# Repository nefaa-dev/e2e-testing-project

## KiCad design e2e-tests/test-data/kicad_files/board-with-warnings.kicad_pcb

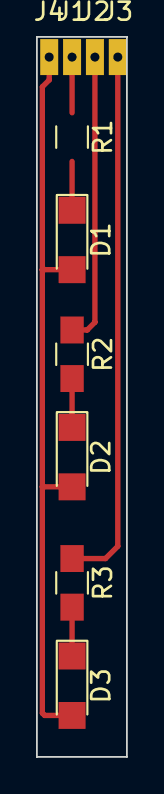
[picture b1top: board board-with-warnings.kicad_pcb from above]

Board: 2 copper layers, 5.0 x 40.0 mm, 10 parts (0 on the bottom side), 5 nets.

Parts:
D1, D2, D3: LED; LED_1206
J1, J2, J3, J4: Conn_01x01; SolderWirePad_single_0-8mmDrill
R1, R2, R3: 47R; R_0805_HandSoldering

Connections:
unnamed: D1.2, D2.2, D3.2, J4.1
unnamed: D2.1, R2.2
unnamed: D3.1, R3.2
unnamed: J2.1, R2.1
unnamed: J3.1, R3.1

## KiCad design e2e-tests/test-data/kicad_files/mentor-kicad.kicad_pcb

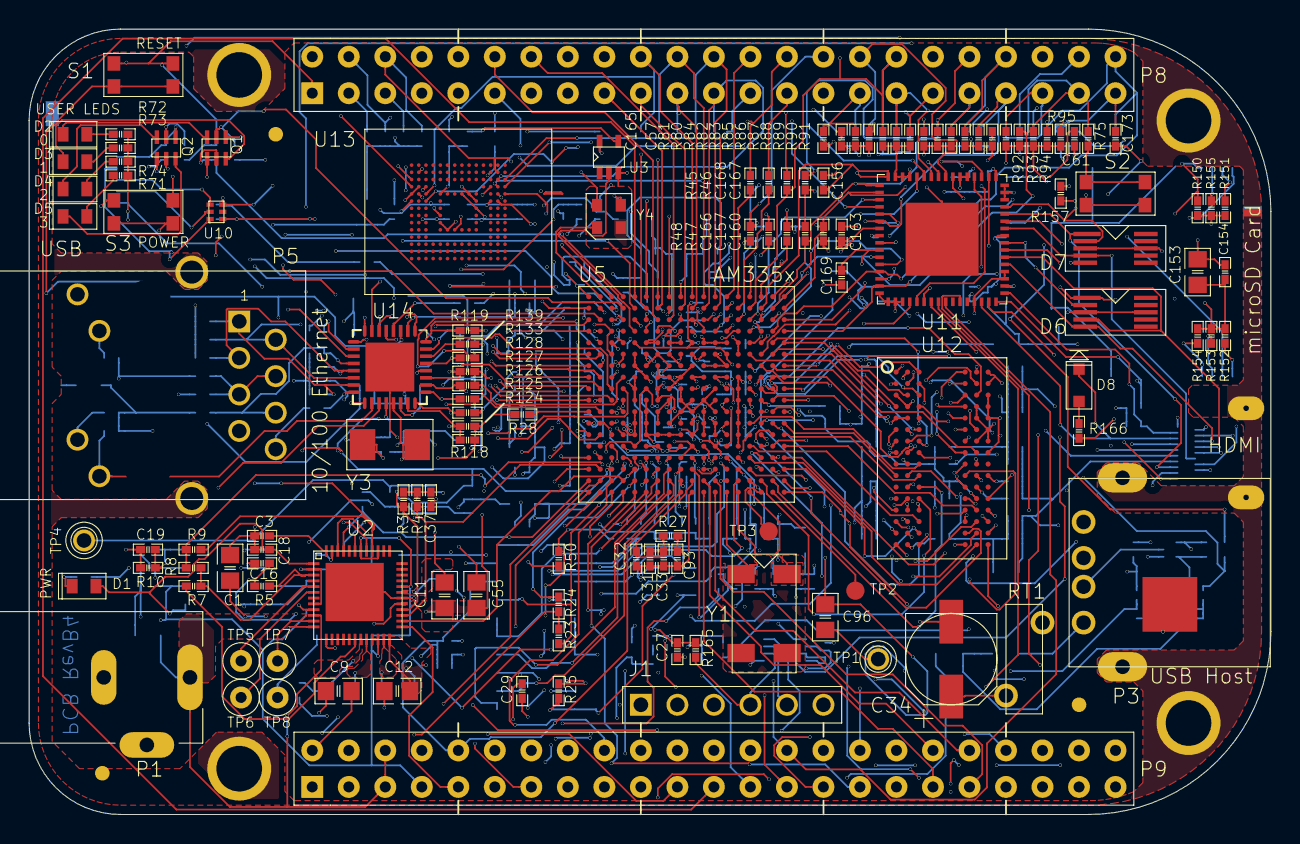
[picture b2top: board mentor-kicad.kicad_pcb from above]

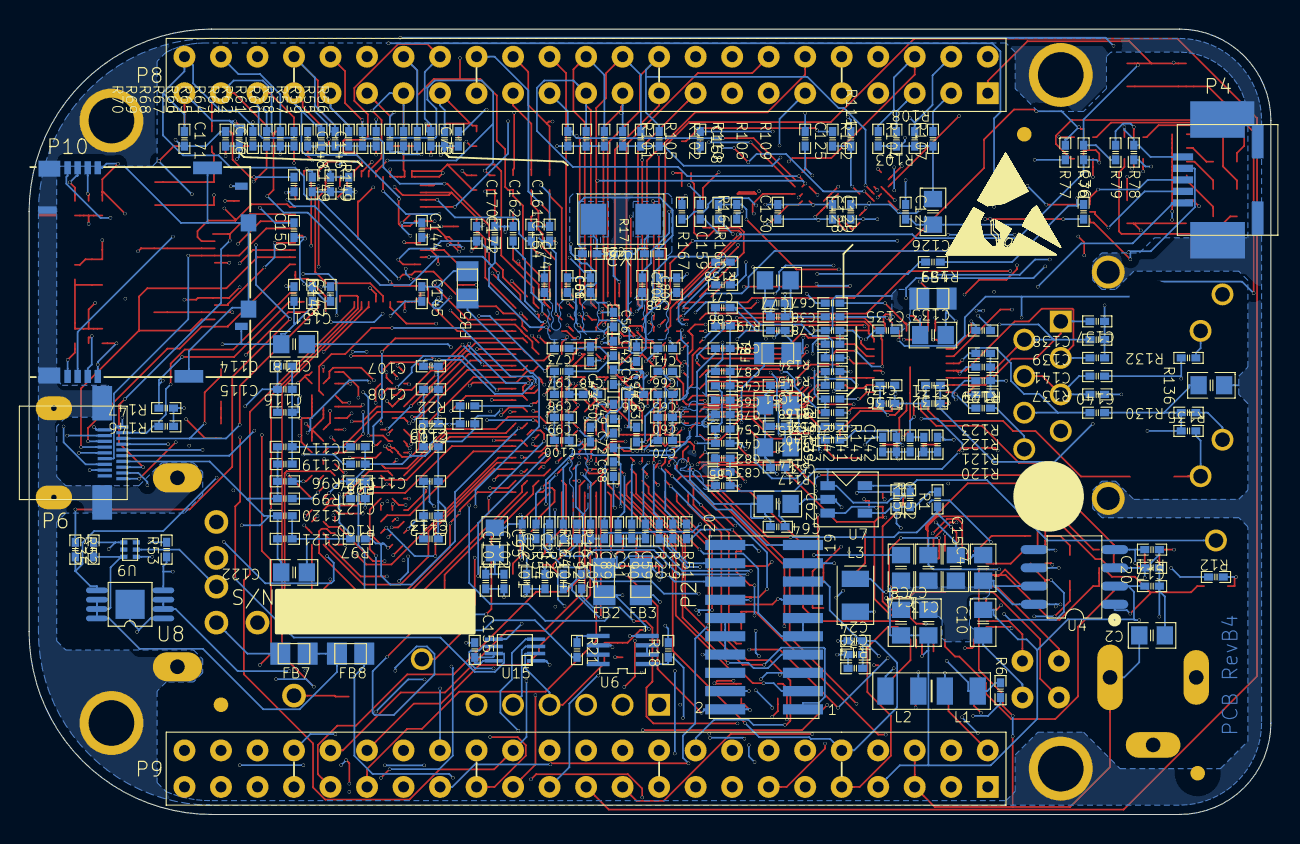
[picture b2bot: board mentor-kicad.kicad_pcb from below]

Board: 6 copper layers, 86.4 x 54.6 mm, 381 parts (250 on the bottom side), 310 nets.

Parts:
C1, C2, C4, C7, C8, C9, C10, C11, C12, C13, C14, C15, C39, C40, C55, C62, C77, C95, C96, C118, C122, C126, C133, C153: 10uF, 10V; 805
C3, C20, C27, C28, C29, C30, C31, C33, C35, C36, C37, C38, C41, C42, C43, C44, C45, C46, C47, C48, C49, C50, C51, C52, C53, C54, C56, C57, C58, C59, C60, C61, C63, C64, C65, C66, C67, C68, C69, C70, C71, C72, C73, C74, C75, C76, C78, C79, C80, C81, C82, C83, C84, C85, C86, C87, C88, C92, C93, C94, C97, C98, C99, C100, C101, C102, C103, C105, C106, C107, C108, C109, C110, C111, C112, C113, C114, C115, C116, C117, C119, C120, C121, C124, C127, C128, C129, C130, C131, C132, C135, C145, C147, C149, C150, C152, C154, C155, C158, C159: 0.1uf, 6V3; 402
C16, C17, C18, C125, C144, C146, C148, C151: 2.2uF, 6V3; 402
C19, C136: 470pF, 50V; 402
C21, C22, C25, C26: 18pF, 50V; 402
C24, C89, C90, C91, C104, C134: 1uF, 10V; 402
C32, C123: 1nF, 50V; 402
C34: 100uF, 6V3; RD205SMD_250D
C137, C138, C139, C140: 15pF, DNI; 402
C141: 0.022uF,10V; 402
C142, C143: 30pF, 50V; 402
C156, C157, C160, C161, C162, C163, C164, C165, C166, C167, C168, C169, C170, C171, C172, C173: 47pF, 6.3V; 402
D1, D2, D3, D4, D5: 598-8170-107F; LED_0603
D6, D7: IP4283CZ10-TT; TSSOP10
D8: RB751V40,115; SOD323
FB1, FB2, FB3, FB4, FB5, FB7: 150OHM800mA; SM-7351-IND-0805
FB8: 0.1 Ohm, 0805; SM-7351-IND-0805
J1: HEADER 6; SIP6
L1, L2, L3: 2.2uH, 2.6A; 2520
MTG1, MTG2, MTG3, MTG4: MHOLE; MTGH200C125D_PL
P1: PJ-200A; CONN3-PWR-PJ102A
P2: CTI JTAG,DNI; HEADER10X2_SMD
P3: USB-A Conn. - 87520-xx1xx; USB_A_SH
P4: mini USB-B; USB5MINI_4SHIELDED_SMD-5
P5: WE_7499010211A; RJ45-7499010211A
P6: 10118241-001RLF; CONN19_HDMI
P8, P9: FEMALE HEADER 2x23; HEADER23X2
P10: MOLEX 502570-001; SD-MICRO-SCHA5B0300
Q1, Q2: DMC56404; SMINI6-F3-B
R1, R56, R65, R66, R67, R68, R76, R77, R78, R79, R80, R82, R83, R84, R85, R86, R87, R88, R89, R94, R95, R165: 100K, 1%; 402
R3, R4, R97, R112, R113, R114, R119, R146, R147: 1.5K, 1%; 402
R5, R6, R7, R8, R19, R20, R27, R49, R50, R51, R137, R142, R149, R159, R160, R161, R162: 0R, 1%; 402
R9: 0R, 1%, DNI; 402
R10: 470K, 5%; 402
R11: 280K, 1%; 402
R12, R71, R72, R73, R74: 820, 5%; 402
R14: 10K, 1%; 402
R17: 1M, 1%; 402
R18, R21, R28, R45, R46, R47, R48, R167: 33, 0402; 402
R22, R120, R121, R122, R123: 49.9, 1%; 402
R23, R24, R25, R26, R163, R164: 4.75K, 1%; 402
R52, R53, R54, R96, R98, R100, R101, R102, R103, R104, R105, R106, R107, R108, R109, R110, R111, R115, R116, R117, R118, R135, R145, R148, R150, R151, R152, R153, R154, R155, R156, R157, R158: 10k, 1%; 402
R55, R57, R59, R69, R81, R90, R91, R92, R93: 100K, 1%, DNI; 402
R58, R60, R61, R62, R63, R64, R70: 100K, 1%,DNI; 402
R75: 100; 402
R99: 240, 1%; 402
R124: 10, 1%,DNI; 402
R125, R126, R127, R128, R129, R131, R133, R134, R138, R139: 100, 1%; 402
R130, R132: 470, 5%; 402
R136: 0.1, 0805; 805
R140: 0R, 1%,DNI; 402
R141: 1M, 1%,DNI; 402
R143: 10, 1%; 402
R144: 12.1K, 1%; 402
R166: 27K, 1%; 402
RT1: PTC_RXEF010; POLYSW200-5638-310
S1, S2, S3: KMR231GLFS; SW4SMD_63X161LS
TP1, TP4: TESTPT1; TP1-8040
TP2, TP3: TESTPT1; TP60C_SMD
TP5, TP6, TP7, TP8: TESTPT1; TP60C33D
U2: TPS65217C; U_48_RSL
U3: SN74LVC1G06DCK; DCK5_2P15X1P4
U4: TL5209; SO8-25X75
U5: IC_AM335X_ZCE_1; AM33XX_15X15
U6: SN74LVC1G74DCTR; SOP8_DCT
U7: 24LC32A; SOT23-5
U8: TPS2051 (DGN); DGN-16X60
U9, U10: TPD4S012; U_6_DRY
U11: TDA19988; QFN64S9X9P5
U12: MT41K256M16HA -125:E; BGA96_T9_P8_9X14
U13: eMMC, 2GB; BGA153_P14_P5_11P5X13
U14: LAN8710A; QFN32_5X5MM_EP3P3MM
U15: SN74LVC2G241; U_8_DCU
Y1: 32.768kHz; XTAL4_126-216SMD
Y2: 24MHz; XTAL150SMD_125X196
Y3: 25.000MHz; XTAL150SMD_125X196
Y4: 24.576MHz; OSC4_61X65LS_79X98SMD

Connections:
12MHZ: R21.2, U11.27
12M_LOOP: U6.2, U6.3
AIN0: P9.39, U5.B6
AIN1: P9.40, U5.C7
AIN2: P9.37, U5.B7
AIN3: P9.38, U5.A7
AIN4: P9.33, U5.C8
AIN5: P9.36, U5.B8
AIN6: P9.35, U5.A8
AIN7: R163.2, R164.1, U5.C9
B_UART0_RX: J1.4, R165.1, U15.2
B_UART0_TX: J1.5, U15.3
CAP_VBB_MPU: C91.1, U5.C10
CAP_VDD_SRAM_CORE: C89.1, U5.D9
CAP_VDD_SRAM_MPU: C90.1, U5.D11
CLKOUT2: P2.18, P9.41, R19.2, R20.1
CLKOUT_SRC: R19.1, U5.D14
CRS: R139.2, U14.14
DDR_A0: U5.F3, U12.N3
DDR_A1: U5.H1, U12.P7
DDR_A2: U5.E4, U12.P3
DDR_A3: U5.C3, U12.N2
DDR_A4: U5.C2, U12.P8
DDR_A5: U5.B1, U12.P2
DDR_A6: U5.D5, U12.R8
DDR_A7: U5.E2, U12.R2
DDR_A8: U5.D4, U12.T8
DDR_A9: U5.C1, U12.R3
DDR_A10: U5.F4, U12.L7
DDR_A11: U5.F2, U12.R7
DDR_A12: U5.E3, U12.N7
DDR_A13: U5.H3, U12.T3
DDR_A14: U5.H4, U12.T7
DDR_A15: U5.D3, U12.M7
DDR_BA0: U5.C4, U12.M2
DDR_BA1: U5.E1, U12.N8
DDR_BA2: U5.B3, U12.M3
DDR_CASN: U5.F1, U12.K3
DDR_CKE: R96.2, U5.G3, U12.K9
DDR_CLK: U5.D2, U12.J7
DDR_CLKN: U5.D1, U12.K7
DDR_CSN: U5.H2, U12.L2
DDR_D0: U5.M3, U12.E3
DDR_D1: U5.M4, U12.F7
DDR_D2: U5.N1, U12.F2
DDR_D3: U5.N2, U12.F8
DDR_D4: U5.N3, U12.H3
DDR_D5: U5.N4, U12.H8
DDR_D6: U5.P3, U12.G2
DDR_D7: U5.P4, U12.H7
DDR_D8: U5.J1, U12.D7
DDR_D9: U5.K1, U12.C3
DDR_D10: U5.K2, U12.C8
DDR_D11: U5.K3, U12.C2
DDR_D12: U5.K4, U12.A7
DDR_D13: U5.L3, U12.A2
DDR_D14: U5.L4, U12.B8
DDR_D15: U5.M1, U12.A3
DDR_DQM0: U5.M2, U12.E7
DDR_DQM1: U5.J2, U12.D3
DDR_DQS0: U5.P1, U12.F3
DDR_DQS1: U5.L1, U12.C7
DDR_DQSN0: U5.P2, U12.G3
DDR_DQSN1: U5.L2, U12.B7
DDR_ODT: U5.G1, U12.K1
DDR_RASN: U5.G4, U12.J3
DDR_RESETN: R97.2, U5.G2, U12.T2
DDR_VREF: C28.1, C123.1, C124.1, R98.2, R100.1, U5.J4, U12.H1, U12.M8
DDR_VTP: R22.2, U5.J3
DDR_WEN: U5.B2, U12.L3
DGND: C1.1, C2.1, C3.1, C4.1, C7.1, C8.1, C9.1, C10.1, C11.1, C12.1, C13.1, C14.1, C15.1, C16.2, C17.2, C18.2, C19.2, C20.2, C24.2, C27.2, C28.2, C29.2, C30.2, C34.2, C35.2, C36.2, C37.2, C38.2, C39.1, C40.1, C41.2, C42.2, C43.2, C44.2, C45.2, C46.2, C47.2, C48.2, C49.2, C50.2, C51.2, C52.2, C53.2, C54.2, C55.1, C56.1, C57.1, C58.2, C59.2, C60.1, C61.1, C62.1, C63.2, C64.2, C65.2, C66.2, C67.2, C68.1, C69.1, C70.1, C71.1, C72.1, C73.1, C74.1, C75.1, C76.1, C77.2, C78.2, C79.2, C80.2, C81.2, C82.2, C83.2, C84.2, C85.2, C86.2, C87.2, C88.2, C89.2, C90.2, C91.2, C92.2, C94.2, C95.1, C96.1, C97.2, C98.2, C99.2, C100.2, C101.2, C102.2, C103.2, C104.2, C105.2, C106.2, C107.2, C108.2, C109.2, C110.2, C111.2, C112.2, C113.2, C114.2, C115.2, C116.2, C117.2, C118.1, C119.2, C120.2, C121.2, C122.1, C123.2, C124.2, C125.2, C126.1, C127.2, C128.2, C129.2, C130.2, C131.2, C132.2, C133.1, C134.2, C135.2, C136.2, C137.2, C138.2, C139.2, C140.2, C141.2, C142.2, C143.2, C144.2, C145.2, C146.2, C147.2, C148.2, C149.2, C150.2, C151.2, C152.2, C153.2, C154.2, C155.1, C156.2, C157.2, C158.2, C159.2, C160.2, C161.2, C162.2, C163.2, C164.2, C165.2, C166.2, C167.2, C168.2, C169.2, C170.2, C171.2, C172.2, C173.2, D6.3, D6.8, D7.3, D7.8, FB3.2, J1.1, P1.2, P2.4, P2.8, P2.10, P2.12, P2.16, P2.20, P3.4, P4.5, P5.8, P6.4, P6.7, P6.10, P6.13, P6.16, P8.1, P8.2, P9.1, P9.2, P9.43, P9.44, P9.45, P9.46, P10.6, P10.9, Q1.1, Q1.4, Q2.1, Q2.4, R10.2, R12.1, R22.1, R25.2, R49.1, R53.2, R54.1, R76.2, R77.2, R78.2, R79.2, R80.2, R81.2, R82.2, R83.2, R84.2, R85.2, R86.2, R87.2, R88.2, R89.2, R90.2, R91.2, R92.2, R93.2, R94.2, R95.2, R96.1, R99.1, R100.2, R115.2, R116.2, R117.2, R118.2, R130.1, R132.1, R135.2, R136.1, R144.2, R145.2, R148.2, R149.2, R164.2, R165.2, S1.1, S1.3, S2.2, S2.4, S3.1, S3.3, TP1.1, TP8.1, U2.30, U2.41, U2.49, U3.3, U4.5, U4.6, U4.7, U4.8, U5.A1, U5.A18, U5.F8, U5.G8, U5.G9, U5.G11, U5.G12, U5.H6, U5.H7, U5.H8, U5.H9, U5.H10, U5.H12, U5.J6, U5.J7, U5.J8, U5.J9, U5.J10, U5.J11, U5.K7, U5.K9, U5.K10, U5.K11, U5.L10, U5.L11, U5.L12, U5.L13, U5.M6, U5.M7, U5.M8, U5.M9, U5.M10, U5.M12, U5.M14, U5.N7, U5.N10, U5.N11, U5.N14, U5.V1, U5.V18, U6.4, U7.2, U8.1, U8.9, U9.4, U10.4, U11.8, U11.9, U11.16, U11.17, U11.18, U11.19, U11.53, U11.54, U11.61, U11.62, U11.63, U11.65, U12.A9, U12.B1, U12.B3, U12.B9, U12.D1, U12.D8, U12.E1, U12.E2, U12.E8, U12.F9, U12.G1, U12.G8, U12.G9, U12.J2, U12.J8, U12.M1, U12.M9, U12.P1, U12.P9, U12.T1, U12.T9, U13.C4, U13.E7, U13.G5, U13.H10, U13.K8, U13.N2, U13.N5, U13.P4, U13.P6, U14.33, U15.1, U15.4, Y4.2
DVI_+5V: P6.19, R146.1, R147.1, RT1.2
EHRPWM1A: P9.14, U5.U14
EHRPWM1B: P9.16, U5.T14
EHRPWM2A: P8.19, U5.U10
EHRPWM2B: P8.13, U5.T10
EMMC_RSTN: R111.2, R162.2, U13.K5
EMMC_VCCI: C125.1, U13.C2
ENZ_KALDO_1P8V: R54.2, U5.B4
ETH_TXD4: R145.1, U14.18
GNDA_ADC: C31.2, C32.2, C33.2, C93.2, FB3.1, P9.34, U5.A9, U5.E8
GND_EARTH: MTG1.1, MTG2.1, MTG3.1, MTG4.1, P3.5, P3.6, P4.6, P4.7, P4.8, P4.9, P5.13, P5.14, P6.20, P6.21, P6.22, P6.23, P10.11, P10.12, P10.13, P10.14, P10.15, P10.16, R136.2
GND_OSC0: C25.2, C26.2, U5.V11
GND_OSC1: C21.1, C22.1, U5.A5
GPIO0_7: P9.42, R50.1, R51.1
GPIO0_7SRC: R50.2, U5.C18
GPIO0_26: P8.14, U5.T11
GPIO0_27: P8.17, U5.U12
GPIO1_12: P8.12, U5.T12
GPIO1_13: P8.11, U5.R12
GPIO1_14: P8.16, U5.V13
GPIO1_15: P8.15, U5.U13
GPIO1_16: P9.15, R160.2, R161.2
GPIO1_17: P9.23, U5.V14
GPIO1_28: P9.12, U5.U18
GPIO1_29: P8.26, U5.V6
GPIO2_1: P8.18, U5.V12
GPIO3_18: R51.2, U5.B12
GPIO3_19: P9.27, U5.C13
GPIO3_20: R20.2, U5.D13
GPIO3_21: P9.25, R167.2, U5.A14
GRNA: P5.9, U14.3
GRN_C: P5.10, R132.2
HDMICLK_DISN: U5.V17, Y4.1
HDMI_1V8: C144.1, C145.1, C146.1, C147.1, C148.1, C149.1, C150.1, C151.1, FB5.1, U11.5, U11.14, U11.29, U11.35, U11.36, U11.41, U11.46, U11.47, U11.48, U11.55
HDMI_CEC: D8.1, P6.15, U11.30
HDMI_CEC_D: D8.2, R166.1
HDMI_DSCL: P6.17, R146.2, U11.33
HDMI_DSDA: P6.18, R147.2, U11.32
HDMI_HPD: P6.1, U11.31
HDMI_INT: R158.2, U5.U16, U11.50
HDMI_SWING: R148.1, U11.34
HDMI_TX0+: D6.2, P6.9, U11.40
HDMI_TX0-: D6.1, P6.11, U11.39
HDMI_TX1+: D7.5, P6.6, U11.43
HDMI_TX1-: D7.4, P6.8, U11.42
HDMI_TX2+: D7.2, P6.3, U11.45
HDMI_TX2-: D7.1, P6.5, U11.44
HDMI_TXC+: D6.4, P6.12, U11.38
HDMI_TXC-: D6.5, P6.14, U11.37
I2C0_SCL: R3.2, U2.28, U5.C16, U7.1, U11.52
I2C0_SDA: R4.2, U2.27, U5.C17, U7.3, U11.51
I2C1_SCL: P9.17, U5.A16
I2C1_SDA: P9.18, U5.B16
I2C2_SCL: P9.19, U5.D17
I2C2_SDA: P9.20, U5.D18
JTAG_EMU0: P2.13, R23.2, U5.C14
JTAG_EMU1: P2.14, R24.2, U5.B14
JTAG_TCK: P2.9, P2.11, U5.A12
JTAG_TDI: P2.3, U5.B11
JTAG_TDO: P2.7, U5.A11
JTAG_TMS: P2.1, U5.C11
JTAG_TRSTN: P2.2, R25.1, U5.B10
LCDDE: R48.1, U5.R6
LCDPCLK: R45.1, U5.V5
LCDVHYNC: R47.1, U5.R5
LCDVSYNC: R46.1, U5.U5
LCD_DATA0: C173.1, P8.45, R70.2, R95.1, U5.R1, U11.15
LCD_DATA1: C171.1, P8.46, R69.2, R94.1, U5.R2, U11.13
LCD_DATA2: C172.1, P8.43, R68.2, R75.1, R93.1, U5.R3, U11.12
LCD_DATA3: C170.1, P8.44, R67.2, R92.1, U5.R4, U11.11
LCD_DATA4: C169.1, P8.41, R66.2, R91.1, U5.T1, U11.10
LCD_DATA5: C163.1, P8.42, R65.2, R90.1, U5.T2, U11.7
LCD_DATA6: C162.1, P8.39, R64.2, R89.1, U5.T3, U11.6
LCD_DATA7: C161.1, P8.40, R63.2, R88.1, U5.T4, U11.3
LCD_DATA8: C160.1, P8.37, R62.2, R87.1, U5.U1, U11.2
LCD_DATA9: C157.1, P8.38, R61.2, R86.1, U5.U2, U11.1
LCD_DATA10: C156.1, P8.36, R60.2, R85.1, U5.U3, U11.64
LCD_DATA11: C168.1, P8.34, R59.2, R84.1, U5.U4, U11.60
LCD_DATA12: C167.1, P8.35, R58.2, R83.1, U5.V2, U11.59
LCD_DATA13: C166.1, P8.33, R57.2, R82.1, U5.V3, U11.58
LCD_DATA14: C165.1, P8.31, R56.2, R81.1, U5.V4, U11.57
LCD_DATA15: C164.1, P8.32, R55.2, R80.1, U5.T5, U11.56
LCD_DE: P8.30, R48.2, U11.20
LCD_HSYNC: P8.29, R47.2, U11.22
LCD_PCLK: P8.28, R45.2, U11.4
LCD_VSYNC: P8.27, R46.2, U11.21
LDO_PGOOD: U2.46, U5.B5
LEDAA: D2.2, R72.2
LEDAC: D2.1, Q1.6
LEDBA: D3.2, R73.2
LEDBC: D3.1, Q1.3
LEDCA: D4.2, R74.2
LEDCC: D4.1, Q2.6
LEDDA: D5.2, R71.2
LEDDC: D5.1, Q2.3
MDIO_CLK: U5.M18, U14.17
MDIO_DATA: R119.2, U5.M17, U14.16
MII1_COL: R138.1, U5.H16
MII1_CRS_DV: R139.1, U5.H17
MII1_REFCLK: R28.2, R124.1, R140.1
MII1_RXCLK: R131.1, U5.L18
MII1_RXD0: R128.1, U5.M16
MII1_RXD1: R127.1, U5.L15
MII1_RXD2: R126.1, U5.L16
MII1_RXD3: R125.1, U5.L17
MII1_RXDV: R129.1, U5.J17
MII1_RXERR: R133.1, U5.J15
MII1_TXCLK: R134.1, U5.K18
MII1_TXD0: U5.K17, U14.22
MII1_TXD1: U5.K16, U14.23
MII1_TXD2: U5.K15, U14.24
MII1_TXD3: U5.J18, U14.25
MII1_TXEN: U5.J16, U14.21
MMC0_CD: P2.19, P10.10, R157.1, U5.C15
MMC0_CLKO: P10.5, R152.2, U5.G17
MMC0_CMD: P10.3, R151.2, U5.G18
MMC0_DAT0: P10.7, R153.2, U5.G16
MMC0_DAT1: P10.8, R154.2, U5.G15
MMC0_DAT2: P10.1, R150.2, U5.F18
MMC0_DAT3: P10.2, R155.2, U5.F17
MMC1_CLK: P8.21, R110.2, U5.U9, U13.M6
MMC1_CMD: P8.20, R109.2, U5.V9, U13.M5
MMC1_DAT0: P8.25, R101.2, U5.U7, U13.A3
MMC1_DAT1: P8.24, R102.2, U5.V7, U13.A4
MMC1_DAT2: P8.5, R103.2, U5.R8, U13.A5
MMC1_DAT3: P8.6, R104.2, U5.T8, U13.B2
MMC1_DAT4: P8.23, R105.2, U5.U8, U13.B3
MMC1_DAT5: P8.22, R106.2, U5.V8, U13.B4
MMC1_DAT6: P8.3, R107.2, U5.R9, U13.B5
MMC1_DAT7: P8.4, R108.2, U5.T9, U13.B6
MODE2: R113.1, R138.2, U14.15
NetC19_1: C19.1, R10.1, R11.2, U4.4
NetR21_1: R21.1, U6.5
NetR75_2: R75.2, S2.1, S2.3
NetR149_1: R149.1, U11.49
NetR159_2: R159.2, U5.P15
NetR162_1: R162.1, U3.4
NetR167_1: R167.1, Y4.3
NetTP5_1: TP5.1, U2.4, U2.5
NetTP6_1: TP6.1, U2.6
NetTP7_1: TP7.1, U2.11
NetU3_2: U3.2, U5.R14
OSC0_IN: C25.1, R17.1, U5.V10, Y2.2
OSC0_OUT: C26.1, R17.2, U5.U11, Y2.1
OSC1_IN: C21.2, U5.A6, Y1.1
OSC1_OUT: C22.2, U5.A4, Y1.4
PHYX: C142.1, R143.2, Y3.2
PHY_VDDCR: C134.1, C136.1, U14.6
PHY_XTAL1: C143.1, R141.2, R142.1, Y3.1
PHY_XTAL2: R141.1, R143.1, U14.4
PMIC_INT: R1.2, U2.45, U5.B18
PMIC_PGOOD: U2.26, U5.B15
PMIC_POWR_EN: U2.9, U5.C6
PROC_A15: R18.1, U5.A15
PWR_BUT: P9.9, S3.2, S3.4, U2.25
PWR_LEDR: D1.1, R12.2
P_BYPASS: C4.2, U2.47
P_INT_LDO: C3.2, U2.48
P_L1: L1.1, U2.20
P_L2: L2.1, U2.23
P_L3: L3.1, U2.31
RBIAS: R144.1, U14.32
RCLKIN: R140.2, R142.2, U14.5
REFCLKO: R118.1, R124.2, R131.2, U14.7
RXD0/MODE0: R112.1, R128.2, U14.11
RXD1/MODE1: R114.1, R127.2, U14.10
RXD2/RMIISEL: R117.1, R126.2, U14.9
RXD3/PHYAD2: R116.1, R125.2, U14.8
RXDV: R129.2, U14.26
RXER/PHYAD0: R115.1, R133.2, U14.13
RXN: C138.1, P5.2, R121.1, U14.30
RXP: C137.1, P5.1, R120.1, U14.31
SPI1_CS0: P9.28, U5.C12, U11.25
SPI1_D0: P9.29, U5.B13, U11.24
SPI1_D1: P9.30, U5.D12
SPI1_SCLK: P9.31, U5.A13, U11.23
SYS_5V: C7.2, C8.2, C10.2, C13.2, C17.1, C34.1, P9.7, P9.8, R71.1, R72.1, R73.1, R74.1, RT1.1, U2.2, U2.7, U2.8, U2.21, U2.22, U2.32, U2.39, U2.42, U4.2, U8.2, U8.3
SYS_RESETN: C24.1, C30.1, P2.15, P9.10, R14.2, S1.2, S1.4, U5.A10, U14.19
TCT_RCT: C141.1, P5.4, P5.5, R137.1
TESTOUT: TP3.1, U5.A3
TIMER4: P8.7, U5.R7
TIMER5: P8.9, U5.T6
TIMER6: P8.10, U5.U6
TIMER7: P8.8, U5.T7
TXCLK: R134.2, U14.20
TXN: C140.1, P5.6, R123.1, U14.28
TXP: C139.1, P5.3, R122.1, U14.29
U5_H18: R28.1, U5.H18
U5_R13: R160.1, U5.R13
U5_T13: R161.1, U5.T13
UART0_RX: U5.E15, U15.6
UART0_TX: U5.E16, U15.5
UART1_RXD: P9.26, U5.D16
UART1_TXD: P9.24, U5.D15
UART2_RXD: P9.22, U5.A17
UART2_TXD: P9.21, U5.B17
UART4_RXD: P9.11, U5.T17
UART4_TXD: P9.13, U5.U17
USB0_DM: P4.2, U5.N18, U10.2
USB0_DP: P4.3, U5.N17, U10.1
USB0_ID: P4.4, U5.P16, U10.3
USB1_DM: P3.2, U5.R18, U9.2
USB1_DP: P3.3, U5.R17, U9.1
USB1_DRVVBUS: R53.1, U5.F15, U8.4
USB1_ID: R49.2, U5.P17
USB1_OCN: R52.2, U5.T16, U8.5
USB1_PWR: C35.1, FB7.1, FB8.2, U8.6, U8.7, U8.8, U9.6
USB1_VBUS: FB8.1, U5.T18
USB_DC: C1.2, C36.1, P4.1, R159.1, U2.12, U10.6
USR0: Q1.2, R76.1, U5.V15
USR1: Q1.5, R77.1, U5.U15
USR2: Q2.2, R78.1, U5.T15
USR3: Q2.5, R79.1, U5.V16
VBUS: FB7.2, P3.1
VDCDC1: L1.2, R6.1, U2.19
VDDS: C80.1, C81.1, C82.1, C83.1, C84.1, C85.1, R8.2, R9.1, U5.E6, U5.E14, U5.F9, U5.K13, U5.N6, U5.P9, U5.P14
VDDS_DDR: C9.2, C95.2, C96.2, C97.1, C98.1, C99.1, C100.1, C101.1, C102.1, C103.1, C107.1, C108.1, C109.1, C110.1, C111.1, C112.1, C113.1, C114.1, C115.1, C116.1, C117.1, C118.2, C119.1, C120.1, C121.1, C122.2, R6.2, R97.1, R98.1, U5.E5, U5.F5, U5.G5, U5.H5, U5.J5, U5.K5, U5.L5, U12.A1, U12.A8, U12.B2, U12.C1, U12.C9, U12.D2, U12.D9, U12.E9, U12.F1, U12.G7, U12.H2, U12.H9, U12.K2, U12.K8, U12.N1, U12.N9, U12.R1, U12.R9
VDD_1V8: C14.2, C78.1, C86.1, C88.1, FB1.1, FB2.2, FB5.2, R9.2, U2.40, U5.D10, U5.E9, U5.N16, U5.R16
VDD_3V3A: C15.2, C27.1, C37.1, C38.1, C56.2, C57.2, C58.1, C59.1, C60.2, C61.2, C66.1, C67.1, C68.2, C69.2, C70.2, C71.2, C72.2, C73.2, C74.2, C75.2, C76.2, C77.1, C87.1, C152.1, C158.1, C159.1, R1.1, R3.1, R4.1, R14.1, R52.1, R55.1, R56.1, R57.1, R58.1, R59.1, R60.1, R61.1, R62.1, R63.1, R64.1, R65.1, R66.1, R67.1, R68.1, R69.1, R70.1, R156.1, U2.43, U3.5, U5.E10, U5.E11, U5.E12, U5.E13, U5.F14, U5.G14, U5.H14, U5.J14, U5.K14, U5.L14, U5.N5, U5.N15, U5.P5, U5.P6, U5.P7, U5.P8, U5.P10, U5.P11, U5.P12, U5.P13, U5.R15, U6.6, U6.7, U6.8, U7.4, Y4.4
VDD_3V3AUX: C18.1, D1.2, U2.1, U4.1
VDD_3V3B: C20.1, C29.1, C126.2, C127.1, C128.1, C129.1, C130.1, C135.1, C153.1, C154.1, C155.2, FB4.1, P2.5, P9.3, P9.4, P10.4, R11.1, R23.1, R24.1, R101.1, R102.1, R103.1, R104.1, R105.1, R106.1, R107.1, R108.1, R109.1, R110.1, R111.1, R112.2, R113.2, R114.2, R119.1, R150.1, R151.1, R152.1, R153.1, R154.1, R155.1, R157.2, R158.1, R163.1, R166.2, U4.3, U13.C6, U13.E6, U13.F5, U13.J10, U13.K9, U13.M4, U13.N4, U13.P3, U13.P5, U14.12, U15.7, U15.8
VDD_5V: C2.2, P1.1, P9.5, P9.6, U2.10
VDD_ADC: C93.1, FB2.1, P9.32, R27.1, U5.D8
VDD_CORE: C11.2, C39.2, C40.2, C41.1, C42.1, C43.1, C44.1, C45.1, C46.1, C47.1, C48.1, C49.1, C50.1, C51.1, C52.1, C53.1, C54.1, C55.2, L3.2, U2.29, U5.F6, U5.F7, U5.G6, U5.G7, U5.G10, U5.H11, U5.J12, U5.K6, U5.K8, U5.K12, U5.L6, U5.L7, U5.L8, U5.L9, U5.M11, U5.M13, U5.N8, U5.N9, U5.N12, U5.N13
VDD_MPU: C12.2, C62.2, C63.1, C64.1, C65.1, L2.2, U2.24, U5.F10, U5.F11, U5.F12, U5.F13, U5.G13, U5.H13, U5.J13
VDD_MPUON: TP2.1, U5.A2
VDD_PHYA: C131.1, C132.1, C133.2, FB4.2, R120.2, R121.2, R122.2, R123.2, R137.2, U14.1, U14.27
VDD_PLL: C79.1, C92.1, C94.1, C106.1, FB1.2, U5.E7, U5.H15, U5.R10, U5.R11
VDD_RTC: C104.1, U5.D6
VIO: R7.2, U2.18
VLDO1: R5.1, R7.1, R8.1, U2.3
VREFP_ADC: C31.1, C32.1, C33.1, R27.2, U5.B9
VRTC: C16.1, C105.1, R5.2, R26.1, U5.D7
WAKEUP: R26.2, U2.13, U5.C5
WP: R156.2, TP4.1, U7.5
XDMA_EVENT_INTR0: P2.17, R18.2, U6.1
YELA: P5.12, R135.1, U14.2
YEL_C: P5.11, R130.2
ZQ: R99.2, U12.L8

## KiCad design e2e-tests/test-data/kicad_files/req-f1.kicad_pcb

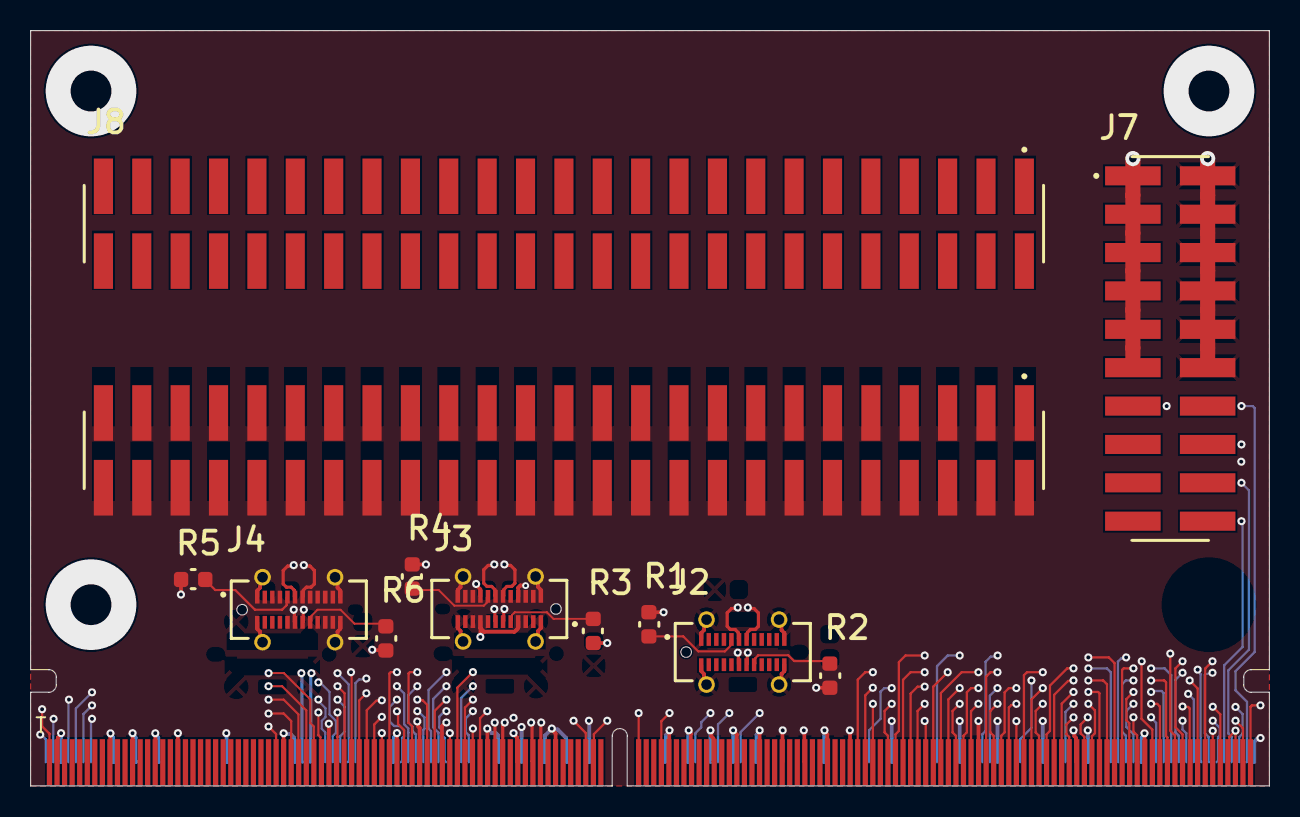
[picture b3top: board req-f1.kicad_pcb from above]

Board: 4 copper layers, 82.0 x 50.0 mm, 12 parts (0 on the bottom side), 122 nets.

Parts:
J1: MXM 3.0; SMARC_EDGE
J2, J3, J4: USB4115-03-C_REVB4; GCT_USB4115-03-C_REVB4
J7: TSM-110-01-L-DV; SAMTEC_TSM-110-01-L-DV
J8: Add 2x TSM-125-01-L-DV to SCH; SAMTEC_TSM-125-01-Ganged
R1, R2, R3, R4, R5, R6: 5.11K; RESC1608X06N

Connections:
ABRD_PWR.EN: J1.S127, J8.14
ABRD_PWR.FAULT: J1.P145, J8.57
BATLOW: J1.S156, J8.55
BOOT_SEL0: J1.P123, J8.71
BOOT_SEL1: J1.P124, J8.72
BOOT_SEL2: J1.P125, J8.74
CARRIER_EN: J1.S154, J8.02
CHARGING: J1.S151, J8.01
CHARGING_PRST: J1.S152, J8.52
DEBUG.RXD: J1.P130, J8.64
DEBUG.TXD: J1.P129, J8.63
FORCE_RECV: J1.S155, J8.56
GAS_EPC.EN1: J1.P114, J8.19
GAS_EPC.EN2: J1.P115, J8.17
GAS_PUMP.EN1: J1.P111, J8.78
GAS_PUMP.EN2: J1.P112, J8.20
GC_HTR_PWM: J1.P113, J8.89
GND: J1.P2, J1.P9, J1.P12, J1.P15, J1.P18, J1.P32, J1.P38, J1.P47, J1.P50, J1.P53, J1.P59, J1.P68, J1.P79, J1.P82, J1.P85, J1.P88, J1.P91, J1.P94, J1.P97, J1.P100, J1.P103, J1.P120, J1.P133, J1.P142, J1.S3, J1.S10, J1.S13, J1.S16, J1.S25, J1.S34, J1.S47, J1.S61, J1.S64, J1.S67, J1.S70, J1.S73, J1.S80, J1.S83, J1.S86, J1.S89, J1.S92, J1.S101, J1.S110, J1.S119, J1.S124, J1.S130, J1.S136, J1.S143, J1.S158, J2.A1, J2.A12, J2.B1, J2.B12, J2.S1, J2.S2, J2.S3, J2.S4, J3.A1, J3.A12, J3.B1, J3.B12, J3.S1, J3.S2, J3.S3, J3.S4, J4.A1, J4.A12, J4.B1, J4.B12, J4.S1, J4.S2, J4.S3, J4.S4, J7.02, J7.04, J7.06, J7.08, J7.10, J7.12, R1.1, R2.2, R3.1, R4.2, R5.1, R6.2
HE_PRES_SW: J1.P108, J8.26
I2C_EXT.SCL: J1.S48, J8.88
I2C_EXT.SDA: J1.S49, J8.35
I2C_INT.SCL: J1.S140, J8.67
I2C_INT.SDA: J1.S139, J8.69
ISO_PWR_EN: J1.S133, J8.08
LID: J1.S148, J8.61
NetJ2_A5: J2.A5, R1.2
NetJ2_B5: J2.B5, R2.1
NetJ3_A5: J3.A5, R3.2
NetJ3_B5: J3.B5, R4.1
NetJ4_A5: J4.A5, R5.2
NetJ4_B5: J4.B5, R6.1
OIL_LV1_CTRL: J1.S51, J8.87
OIL_OS1: J1.P78, J8.28
OIL_OS2: J1.S52, J8.33
OIL_PUMP.DIR: J1.S38, J8.45
OIL_PUMP.EN: J1.S50, J8.34
OIL_PUMP.FAULT: J1.P109, J8.25
OIL_PUMP.TACK: J1.S53, J8.81
PCIE_B_REF_CK+: J1.S84, J8.27
PCIE_B_TX+: J1.S90, J8.80
PCIE_B_TX-: J1.S87, J8.82
POWER_BTN: J1.P128, J8.79
RESET_IN: J1.P127, J8.73
ROTARY.6/10P_SEL: J1.P118, J8.77
ROTARY.DIR: J1.P105, J8.86
ROTARY.EN: J1.P119, J8.16
ROTARY.FAULT: J1.P104, J8.29
ROTARY.HOME: J1.S39, J8.93
ROTARY.OPTO_6P: J1.P116, J8.83
ROTARY.OPTO_10P: J1.P117, J8.18
ROTARY.RESET: J1.P106, J8.24
ROTARY.STEP: J1.S122, J8.76
RS232.CTS: J1.P139, J8.60
RS232.DCD: J1.P146, J8.53
RS232.DSR: J1.P144, J8.59
RS232.DTR: J1.P143, J8.54
RS232.INV: J1.S123, J8.15
RS232.RI: J1.S142, J8.07
RS232.RTS: J1.P138, J8.13
RS232.RXD: J1.P137, J8.10
RS232.TXD: J1.P136, J8.58
RS485.DXEN: J1.P131, J8.65
RS485.RXD: J1.P135, J8.75
RS485.RXEN: J1.P132, J8.70
RS485.SEL: J1.S116, J8.12
RS485.TXD: J1.P134, J8.06
SD2_CD: J1.P35, J8.44
SD2_CLK: J1.P36, J8.94
SD2_CMD: J1.P34, J8.46
SD2_D1: J1.P40, J8.96
SD2_D2: J1.P41, J8.95
SD2_D3: J1.P42, J8.92
SD2_WP: J1.P33, J8.98
SD_D0: J1.P39, J8.43
SLEEP: J1.S149, J8.09
SMB_ALERT_1V8: J1.P1, J8.49
SPI.CLK: J1.P44, J8.90
SPI.DAC1_CS: J1.S40, J8.42
SPI.DAC2_CS: J1.S42, J8.39
SPI.MISO: J1.P45, J8.41
SPI.MOSI: J1.P46, J8.38
SPI.RTC_CS: J1.P31, J8.97
SPI.TCD_CS: J1.P43, J8.91
SPI.TCD_DRDY: J1.S41, J8.40
SYS_RESET: J1.P126, J8.66
SYS_SHUTDOWN: J1.P110, J8.23
TEST: J1.S157, J8.51
TP1: J1.P72, J1.S5, J8.47
TP2: J1.P73, J1.S7, J8.50
TP3: J1.S1, J1.S4, J8.100
TP4: J1.P37, J1.S2, J8.99
TP5: J1.S6, J1.S54, J8.48
TP6: J1.P52, J8.84
TP7: J1.P51, J8.85
TP8: J1.P49, J8.37
TP9: J1.P48, J8.36
TP10: J1.S153, J8.03
TP11: J1.P122, J8.21
TP12: J1.P121, J8.11
TP13: J1.S146, J8.04
TP14: J1.P58, J8.31
TP15: J1.P57, J8.32
TP16: J1.S56, J7.16
TP17: J1.S57, J7.18
TP18: J1.P56, J7.17
TP19: J1.P54, J7.13
TP20: J1.P55, J7.15
TP21: J1.P140, J7.19
TP22: J1.P141, J7.20
USB0D_N: J1.P61, J3.A7, J3.B7
USB0D_P: J1.P60, J3.A6, J3.B6
USB0_VBUS: J1.P63, J1.P147, J1.P148, J1.P149, J1.P150, J1.P151, J1.P152, J1.P153, J1.P154, J1.P155, J1.P156, J3.A4, J3.A9, J3.B4, J3.B9, J7.01, J7.03, J7.05, J7.07, J7.09, J7.11
USB1D_N: J1.P66, J2.A7, J2.B7
USB1D_P: J1.P65, J2.A6, J2.B6
USB4D_N: J1.S36, J4.A7, J4.B7
USB4D_P: J1.S35, J4.A6, J4.B6
VDD_RTC: J1.S147, J7.14
VIN_PWR_BAD: J1.S150, J8.62
WDT_EN: J1.S107, J8.22
WDT_FEED: J1.S141, J8.05
WDT_RESET: J1.P75, J8.30
WDT_TIME_OUT: J1.S145, J8.68

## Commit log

2025-04-26 add e2e testing project

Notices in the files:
e2e-tests/test-data/kicad_files/mentor-kicad.kicad_pcb:
To view a copy of this license, visit http://creativecommons.org/licenses/by-sa/3.0/ or send
For more information, see http://creativecommons.org/license/results-one?license_code=by-sa
This work is licensed under the Creative Commons Attribution-Share Alike 3.0 Unported License.
a letter to Creative Commons, 171 Second Street, Suite 300, San Francisco, California, 94105, USA.
